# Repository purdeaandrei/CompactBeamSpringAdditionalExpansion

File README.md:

# Compact Beamspring controller.

This controller only supports new style card edge connectors only, and it requires the side
of the card edge connector to be cut off, and the pins be bent 90 degress.

This is a variant of the controller that also includes an additional expansion header, designed
especially for 3278 A02 / 3279 2C keyboards with a top panel, sporting additional leds and
non-capacitive push buttons.
See https://github.com/purdeaandrei/CompactBeamSpring/issues/1 for some details about these keyboards.

See [top_panel_modifications.md](top_panel_modifications.md) for instructions on how to connect this controller
to the top panel of your 3278 A02 / 3279 2C keyboard.

## Images

## Other controllers in this family:
* https://github.com/purdeaandrei/CompactBeamSpring
* https://github.com/purdeaandrei/SMDModelFController
* https://github.com/purdeaandrei/SMDModelFController/tree/extra_columns
* https://github.com/purdeaandrei/SMD4704KishsaverClassModelFController
* https://github.com/listofoptions/TH-XWhatsIt

## Origins and license

This project is based on the Through-hole xwhatsit by listofoptions, which is un turn
based on the capsense controllers by XWhatsIt
(Tom Wong-Cornall). original liscencure holds, as well as CERN OSH
(compatible license).

original implementation of Tom Wong-Cornall's controller documented here

http://downloads.cornall.co/ibm-capsense-usb-web/ibm-capsense-usb.html

Working theory of operation is under the previous link.

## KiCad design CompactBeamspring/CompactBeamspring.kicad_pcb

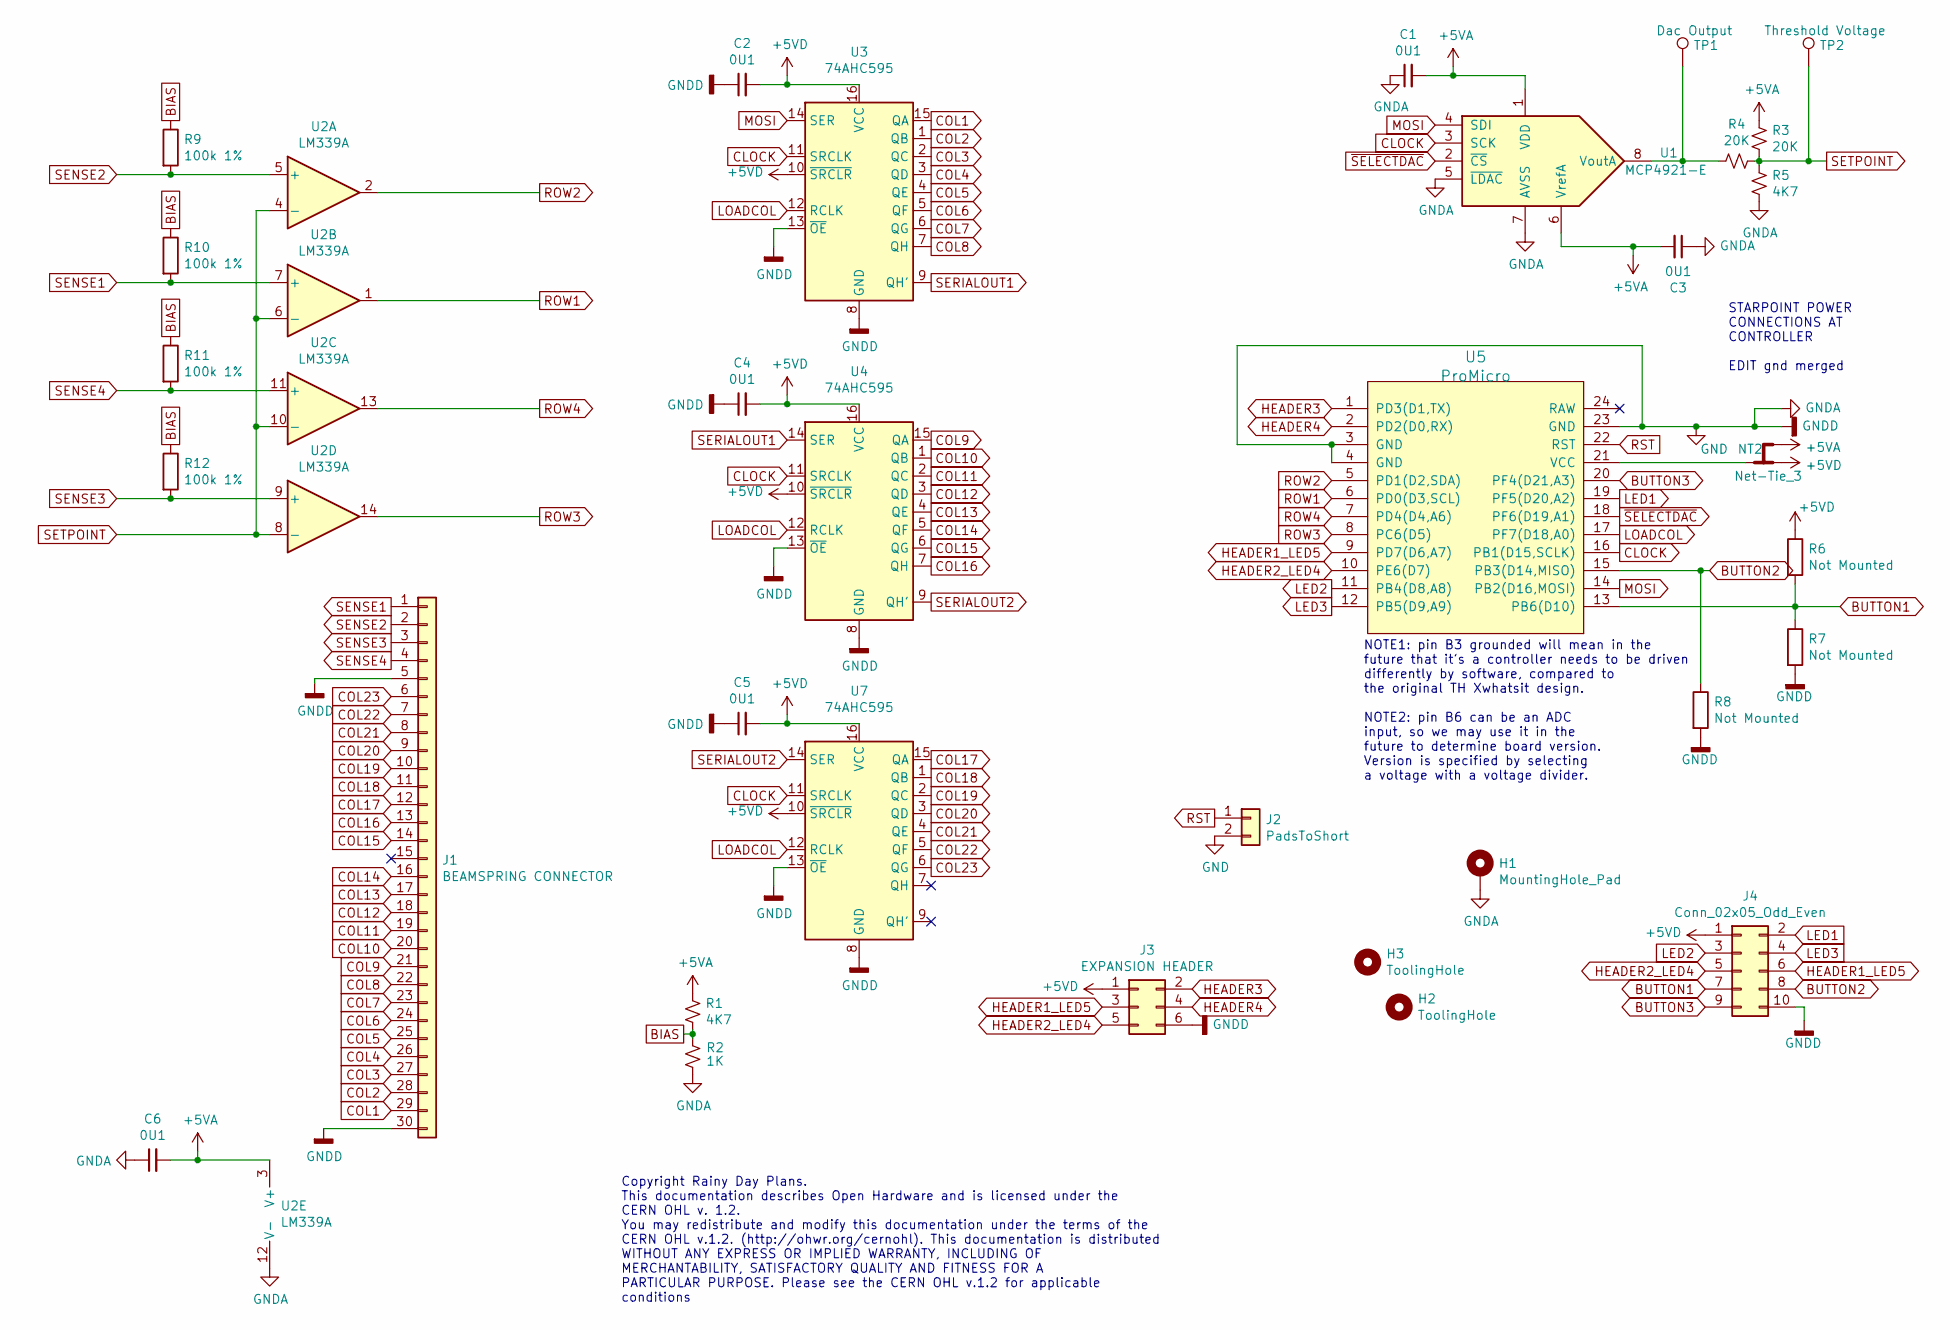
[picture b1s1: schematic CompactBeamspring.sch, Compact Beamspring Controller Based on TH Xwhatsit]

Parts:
C1, C2, C3, C4, C5, C6: 0U1; C_0805_2012Metric_Pad1.15x1.40mm_HandSolder; LCSC C49678
H1: MountingHole_Pad; ChassisGnd
H2, H3: ToolingHole; tooling_hole
J1: BEAMSPRING CONNECTOR; 30-pin-universal-beamspring-connector_v3_onlyflat
J2: PadsToShort
J3: EXPANSION HEADER; PinHeader_2x03_P2.54mm_Vertical
J4: Conn_02x05_Odd_Even; PinHeader_2x05_P2.54mm_Vertical
NT2: Net-Tie_3; NetTie-3_THT_Pad0.3mm
R1, R5: 4K7; R_0805_2012Metric_Pad1.15x1.40mm_HandSolder; LCSC C17673
R2: 1K; R_0805_2012Metric_Pad1.15x1.40mm_HandSolder; LCSC C17513
R3, R4: 20K; R_0805_2012Metric_Pad1.15x1.40mm_HandSolder; LCSC C4328
R6, R7, R8: Not Mounted; R_0805_2012Metric_Pad1.15x1.40mm_HandSolder
R9, R10, R11, R12: 100k 1%; R_0805_2012Metric_Pad1.15x1.40mm_HandSolder; LCSC C17407
TP1: Dac Output; TestPoint_Pad_D1.0mm
TP2: Threshold Voltage; TestPoint_Pad_D1.0mm
U1: MCP4921-E; SOIC-8_3.9x4.9mm_P1.27mm; LCSC C43499
U2: LM339A; SOIC-14_3.9x8.7mm_P1.27mm; LCSC C74559
U3, U4, U7: 74AHC595; SOIC-16_3.9x9.9mm_P1.27mm; LCSC C5520
U5: ProMicro

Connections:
+5VA: C1.2, C3.2, C6.2, NT2.3, R1.1, R3.2, U1.1 (VDD), U1.6 (VrefA), U2.3 (V+)
+5VD: C2.2, C4.2, C5.2, J3.1, J4.1, NT2.1, R6.1, U3.10 (~SRCLR), U3.16 (VCC), U4.10 (~SRCLR), U4.16 (VCC), U7.10 (~SRCLR), U7.16 (VCC)
BIAS: R1.2, R2.2, R9.1, R10.1, R11.1, R12.1
BUTTON1: J4.7, R6.2, R7.1, U5.13 (PB6(D10))
BUTTON2: J4.8, R8.1, U5.15 (PB3(D14,MISO))
BUTTON3: J4.9, U5.20 (PF4(D21,A3))
CLOCK: U1.3 (SCK), U3.11 (SRCLK), U4.11 (SRCLK), U5.16 (PB1(D15,SCLK)), U7.11 (SRCLK)
COL1: J1.29, U3.15 (QA)
COL2: J1.28, U3.1 (QB)
COL3: J1.27, U3.2 (QC)
COL4: J1.26, U3.3 (QD)
COL5: J1.25, U3.4 (QE)
COL6: J1.24, U3.5 (QF)
COL7: J1.23, U3.6 (QG)
COL8: J1.22, U3.7 (QH)
COL9: J1.21, U4.15 (QA)
COL10: J1.20, U4.1 (QB)
COL11: J1.19, U4.2 (QC)
COL12: J1.18, U4.3 (QD)
COL13: J1.17, U4.4 (QE)
COL14: J1.16, U4.5 (QF)
COL15: J1.14, U4.6 (QG)
COL16: J1.13, U4.7 (QH)
COL17: J1.12, U7.15 (QA)
COL18: J1.11, U7.1 (QB)
COL19: J1.10, U7.2 (QC)
COL20: J1.9, U7.3 (QD)
COL21: J1.8, U7.4 (QE)
COL22: J1.7, U7.5 (QF)
COL23: J1.6, U7.6 (QG)
GND: C1.1, C2.1, C3.1, C4.1, C5.1, C6.1, H1.1, J1.5, J1.30, J2.2, J3.6, J4.10, R2.1, R5.1, R7.2, R8.2, U1.5 (~LDAC~), U1.7 (AVSS), U2.12 (V-), U3.8 (GND), U3.13 (~OE), U4.8 (GND), U4.13 (~OE), U5.3 (GND), U5.4 (GND), U5.23 (GND), U7.8 (GND), U7.13 (~OE)
HEADER1_LED5: J3.3, J4.6, U5.9 (PD7(D6,A7))
HEADER2_LED4: J3.5, J4.5, U5.10 (PE6(D7))
HEADER3: J3.2, U5.1 (PD3(D1,TX))
HEADER4: J3.4, U5.2 (PD2(D0,RX))
LED1: J4.2, U5.19 (PF5(D20,A2))
LED2: J4.3, U5.11 (PB4(D8,A8))
LED3: J4.4, U5.12 (PB5(D9,A9))
LOADCOL: U3.12 (RCLK), U4.12 (RCLK), U5.17 (PF7(D18,A0)), U7.12 (RCLK)
MOSI: U1.4 (SDI), U3.14 (SER), U5.14 (PB2(D16,MOSI))
unnamed: NT2.2, U5.21 (VCC)
unnamed: R4.2, TP1.1, U1.8 (VoutA)
ROW1: U2.1, U5.6 (PD0(D3,SCL))
ROW2: U2.2, U5.5 (PD1(D2,SDA))
ROW3: U2.14, U5.8 (PC6(D5))
ROW4: U2.13, U5.7 (PD4(D4,A6))
RST: J2.1, U5.22 (RST)
SENSE1: J1.1, R10.2, U2.7 (+)
SENSE2: J1.2, R9.2, U2.5 (+)
SENSE3: J1.3, R12.2, U2.9 (+)
SENSE4: J1.4, R11.2, U2.11 (+)
SERIALOUT1: U3.9 (QH'), U4.14 (SER)
SERIALOUT2: U4.9 (QH'), U7.14 (SER)
SETPOINT: R3.1, R4.1, R5.2, TP2.1, U2.4 (-), U2.6 (-), U2.8 (-), U2.10 (-)
~SELECTDAC: U1.2 (~CS~), U5.18 (PF6(D19,A1))

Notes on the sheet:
Copyright Rainy Day Plans. This documentation describes Open Hardware and is licensed under the CERN OHL v. 1.2. You may redistribute and modify this documentation under the terms of the CERN OHL v.1.2. (http://ohwr.org/cernohl). This documentation is distributed WITHOUT ANY EXPRESS OR IMPLIED WARR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
NOTE1: pin B3 grounded will mean in the future that it's a controller needs to be driven differently by software, compared to the original TH Xwhatsit design. NOTE2: pin B6 can be an ADC input, so we may use it in the future to determine board version. Version is specified by selecting a voltage wi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
STARPOINT POWER CONNECTIONS AT CONTROLLER EDIT gnd merged

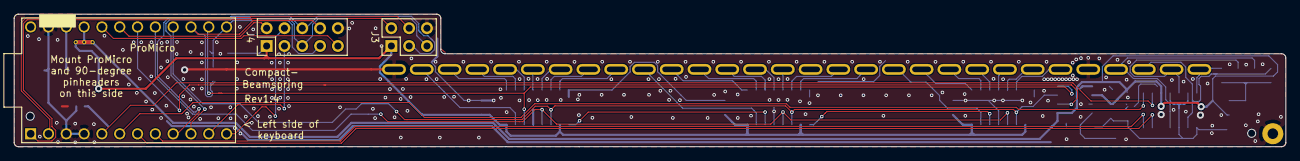
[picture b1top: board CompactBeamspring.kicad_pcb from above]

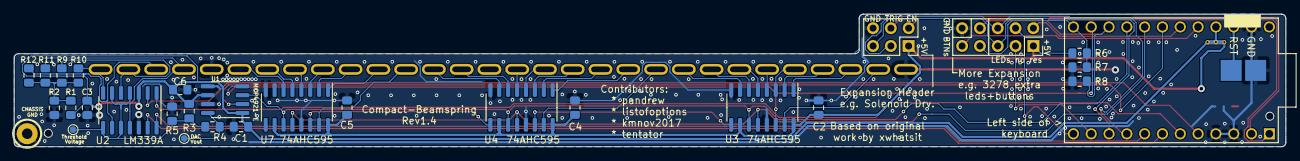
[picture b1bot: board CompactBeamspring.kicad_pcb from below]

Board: 2 copper layers, 181.3 x 18.9 mm, 34 parts (28 on the bottom side), 55 nets.

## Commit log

2021-10-30 Updated to rev. 1.4
2022-05-28 Update component rotations, to match new behaviour of JLCPCB on the bottom layer
2022-05-28 Updated renders
2022-05-28 Added document to describe top panel modifications
2022-05-28 Panel modification updates
2022-05-28 Added some sources for components
2022-07-31 Updated shift register and 100k resistor LCSC part numbers
2022-07-31 fix rotations to match latest JLCPCB behaviour
2022-09-15 Revert part of commit 'Updated 100k resistor and shift register LCSC part numbers' (the shift register BOM changes only)

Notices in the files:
CompactBeamspring/CompactBeamspring.kicad_pcb:
Licenced under CERN OHL Version 1.2
